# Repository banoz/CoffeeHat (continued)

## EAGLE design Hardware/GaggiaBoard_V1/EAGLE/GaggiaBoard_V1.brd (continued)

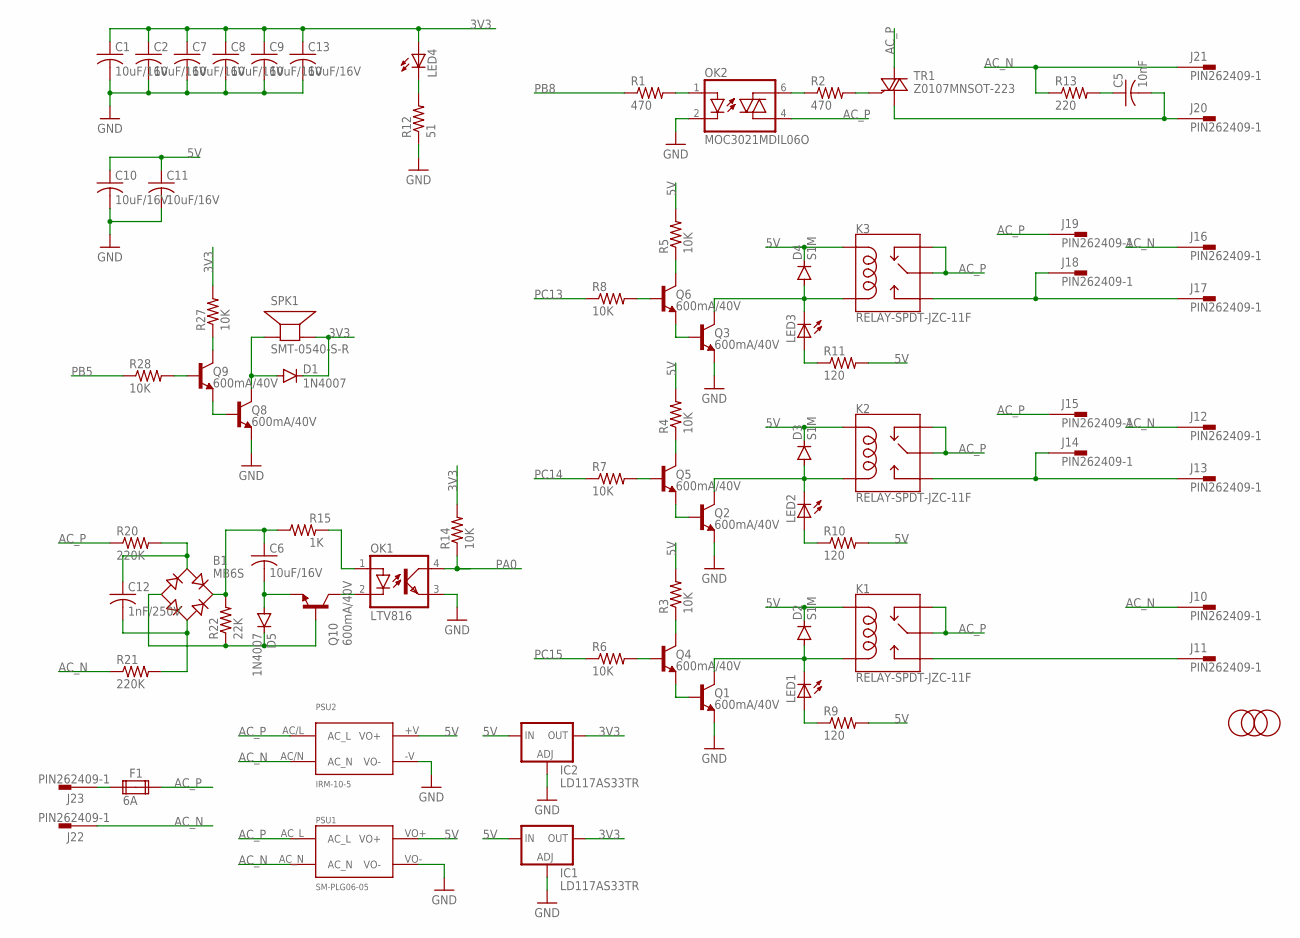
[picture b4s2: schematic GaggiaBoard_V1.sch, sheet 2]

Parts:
B1: MB6S; SOIC-4; LCSC C2487
C1, C2, C6, C7, C8, C9, C10, C11, C13: 10uF/16V; C0603; LCSC C86275
C5: 10nF; C1206; LCSC C107192
C12: 1nF/250V; C0603; LCSC C277510
D1, D5: 1N4007; DO214AC; LCSC C727081
D2, D3, D4: S1M; SMA; LCSC C155378
F1: 6A; FUSE1; LCSC C206887
IC1, IC2: LD117AS33TR; SOT223; LCSC C152529
J10, J11, J12, J13, J14, J15, J16, J17, J18, J19, J20, J21, J22, J23: PIN262409-1; 62409-1; LCSC C86495
K1, K2, K3: RELAY-SPDT-JZC-11F; RELAY-JZC; LCSC C74541
LED1, LED2, LED3, LED4: LEDCHIPLED_1206; CHIPLED_1206; LCSC C375534
MARK3, MARK4, MARK6: FIDUCIAL; FIDUCIAL_1MM
OK1: LTV816; DIL04; LCSC C2944043
OK2: MOC3021MDIL06O; DIL06O; LCSC C5242
PSU1: SM-PLG06-05; SM-PLG06
PSU2: IRM-10-5; IRM-10
Q1, Q2, Q3, Q4, Q5, Q6, Q8, Q9, Q10: 600mA/40V; SOT23-3; LCSC C82460
R1, R2: 470; R0603; LCSC C114669
R3, R4, R5, R6, R7, R8, R14, R27, R28: 10K; R0603; LCSC C98220
R9, R10, R11: 120; R0603; LCSC C114640
R12: 51; R0603; LCSC C114628
R13: 220; R2512; LCSC C877859
R15: 1K; R0603; LCSC C22548
R20, R21: 220K; R1206; LCSC C130275
R22: 22K; R0603; LCSC C114065
SPK1: SMT-0540-S-R; LCSC C391029
TR1: Z0107MNSOT-223; SOT223; LCSC C71218

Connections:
3V3: C1.1, C2.1, C7.1, C8.1, C9.1, C13.1, D1.C, IC1.4 (OUT), IC2.4 (OUT), LED4.A, R14.2, R27.2, SPK1.+ (-); also elsewhere on the board
3WAY: J11.A1, J11.A2, K1.3 (NO)
5V: C10.1, C11.1, D2.C, D3.C, D4.C, IC1.3 (IN), IC2.3 (IN), K1.5 (COIL1), K2.5 (COIL1), K3.5 (COIL1), PSU1.VO+, PSU2.+V (VO+), R3.2, R4.2, R5.2, R9.2, R10.2, R11.2; also elsewhere on the board
AC_N: J10.A1, J10.A2, J12.A1, J12.A2, J16.A1, J16.A2, J21.A1, J21.A2, J22.A1, J22.A2, PSU1.AC_N, PSU2.AC/N (AC_N), R13.1, R21.1
AC_P: F1.2A, J15.A1, J15.A2, J19.A1, J19.A2, K1.2 (NC), K1.4 (MAIN), K2.2 (NC), K2.4 (MAIN), K3.2 (NC), K3.4 (MAIN), OK2.4 (A1), PSU1.AC_L, PSU2.AC/L (AC_L), R20.1, TR1.2 (A2), TR1.4 (A2)
GND: C1.2, C2.2, C7.2, C8.2, C9.2, C10.2, C11.2, C13.2, IC1.1 (ADJ), IC2.1 (ADJ), OK1.3 (EMIT), OK2.2 (C), PSU1.VO-, PSU2.-V (VO-), Q1.2 (E), Q2.2 (E), Q3.2 (E), Q8.2 (E), R12.1; also elsewhere on the board
HEATER_1: J13.A1, J13.A2, J14.A1, J14.A2, K2.3 (NO)
HEATER_2: J17.A1, J17.A2, J18.A1, J18.A2, K3.3 (NO)
unnamed: F1.1A, J23.A1, J23.A2
unnamed: B1.-, D5.C, Q10.1 (B), R22.1
unnamed: OK1.2 (C), Q10.3 (C)
unnamed: OK2.6 (A2), R2.1
unnamed: R2.2, TR1.3 (G)
unnamed: D2.A, K1.1 (COIL2), LED1.C, Q1.3 (C)
unnamed: D3.A, K2.1 (COIL2), LED2.C, Q2.3 (C)
unnamed: D4.A, K3.1 (COIL2), LED3.C, Q3.3 (C)
unnamed: Q1.1 (B), Q4.2 (E)
unnamed: Q2.1 (B), Q5.2 (E)
unnamed: Q3.1 (B), Q6.2 (E)
unnamed: Q6.1 (B), R8.2
unnamed: Q6.3 (C), R5.1
unnamed: Q5.3 (C), R4.1
unnamed: Q5.1 (B), R7.2
unnamed: Q4.3 (C), R3.1
unnamed: Q4.1 (B), R6.2
unnamed: LED1.A, R9.1
unnamed: LED4.C, R12.2
unnamed: LED2.A, R10.1
unnamed: LED3.A, R11.1
unnamed: D1.A, Q8.3 (C), SPK1.- (+)
unnamed: C5.1, R13.2
unnamed: Q8.1 (B), Q9.2 (E)
unnamed: Q9.1 (B), R28.2
unnamed: Q9.3 (C), R27.1
unnamed: B1.~1 (AC1), C12.2, R21.2
unnamed: B1.~2 (AC2), C12.1, R20.2
unnamed: OK2.1 (A), R1.2
unnamed: C6.2, D5.A, Q10.2 (E)
unnamed: OK1.1 (A), R15.2
unnamed: B1.+, C6.1, R15.1, R22.2
PA0: OK1.4 (COL), R14.1; also elsewhere on the board
PB5: R28.1; also elsewhere on the board
PB8: R1.1; also elsewhere on the board
PC13: R8.1; also elsewhere on the board
PC14: R7.1; also elsewhere on the board
PC15: R6.1; also elsewhere on the board
PUMP_P: C5.2, J20.A1, J20.A2, TR1.1 (A1)

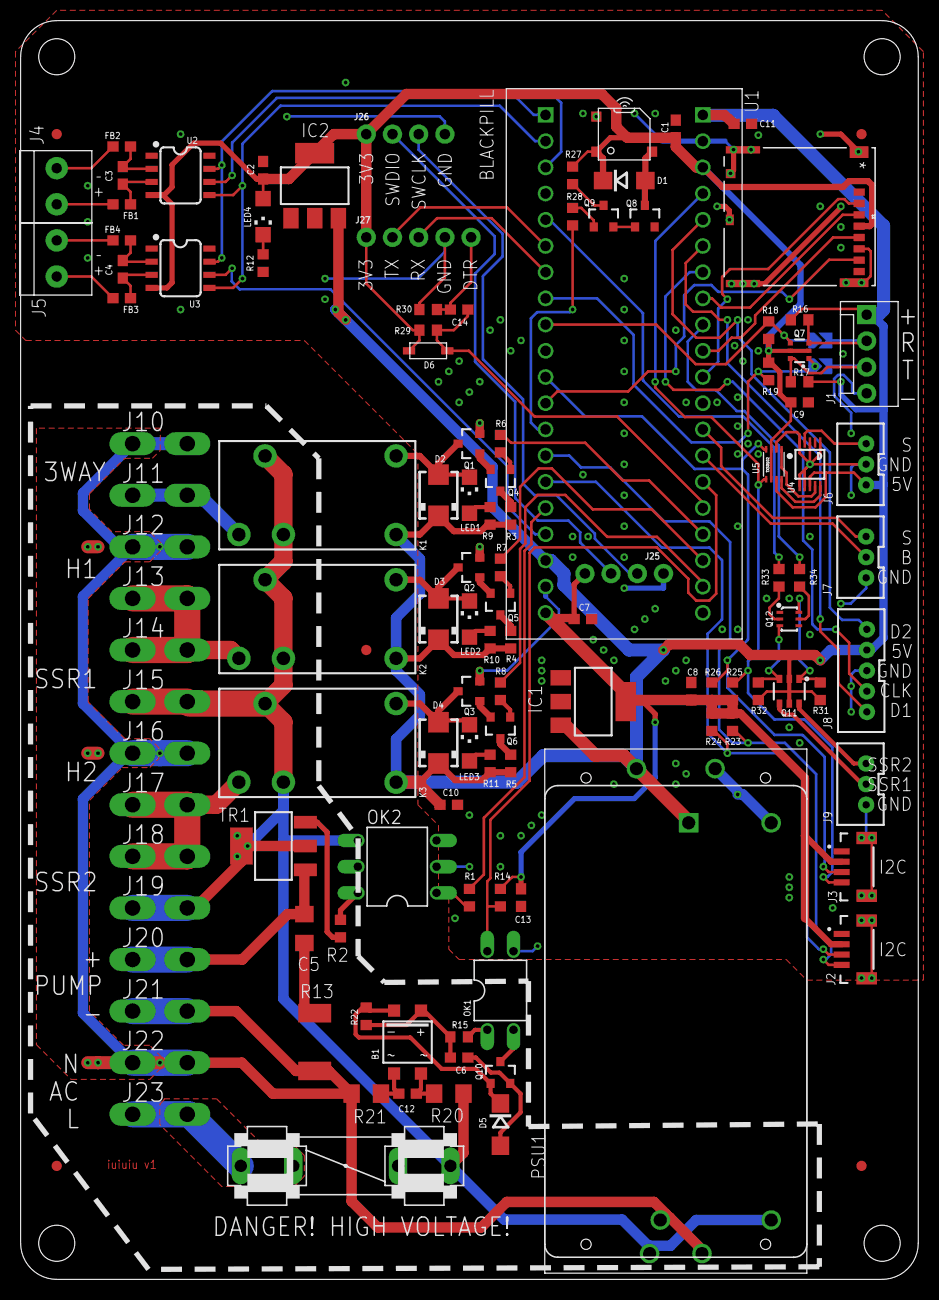
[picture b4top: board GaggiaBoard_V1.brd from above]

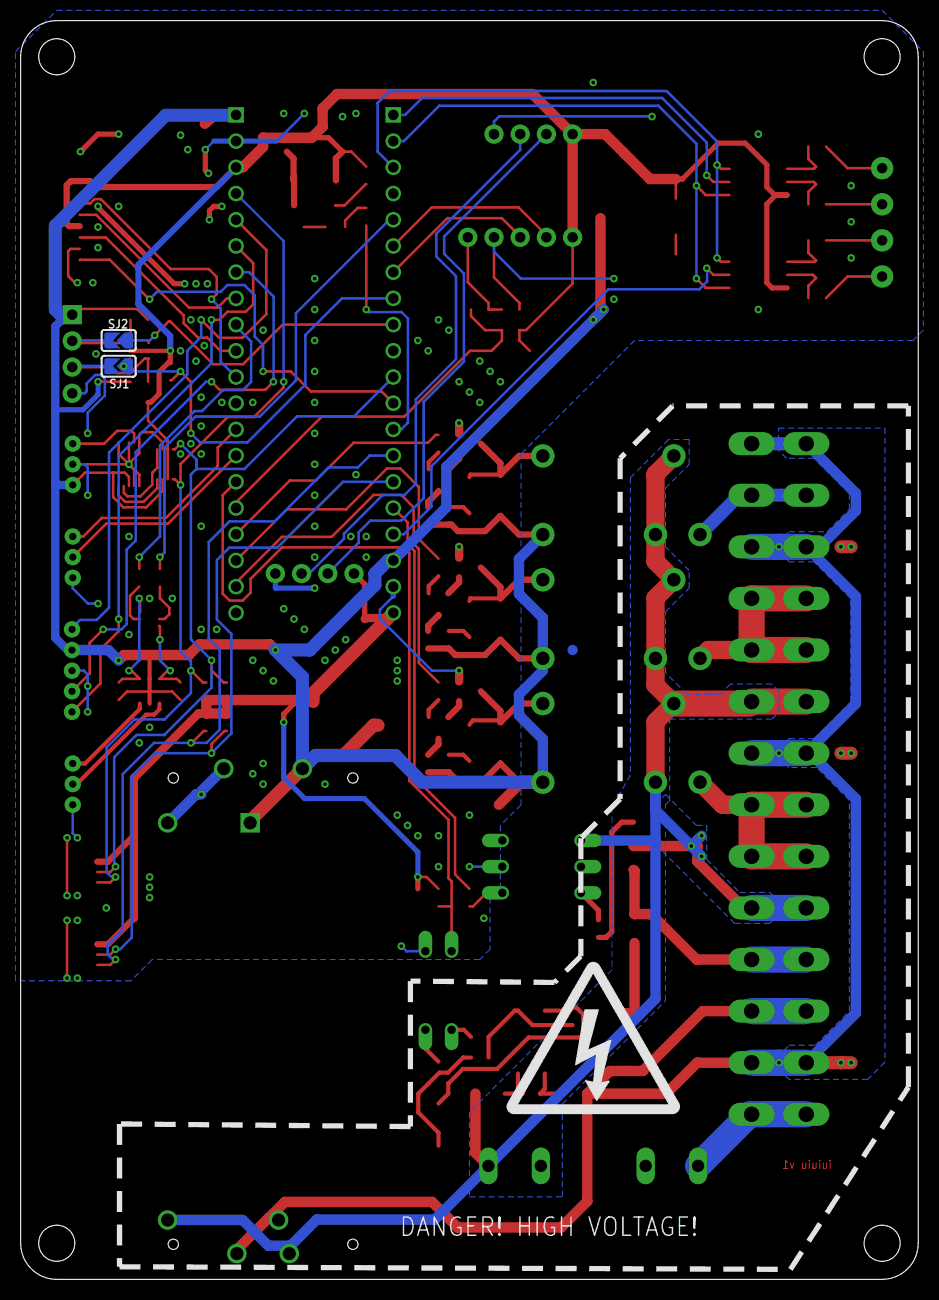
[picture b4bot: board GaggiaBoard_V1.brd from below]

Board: 2 copper layers, 87.0 x 122.0 mm, 128 parts (4 on the bottom side), 93 nets.

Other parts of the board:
U$1: HV_LOGO_3

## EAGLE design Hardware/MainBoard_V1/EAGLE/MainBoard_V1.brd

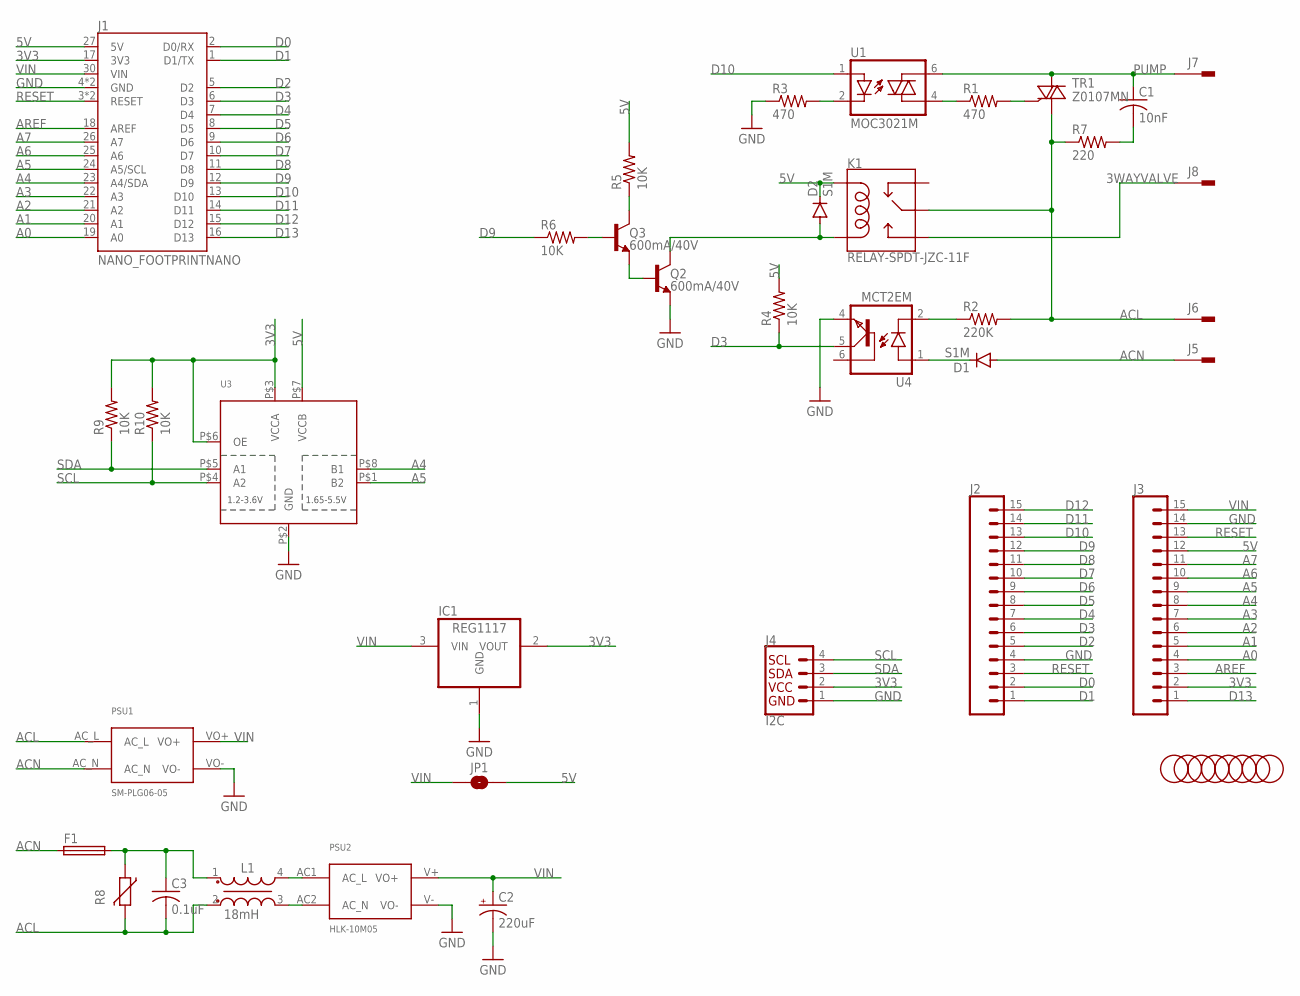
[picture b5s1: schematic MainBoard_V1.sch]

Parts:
C1: 10nF; C075-032X103; LCSC C2893639
C2: 220uF; E2,5-6
C3: 0.1uF; C150-054X183
D1, D2: S1M; SMA; LCSC C155378
F1: FUSETE5; TE5
IC1: REG1117; SOT223; LCSC C26537
J1: NANO_FOOTPRINTNANO; NANO
J2, J3: CONN_15; 1X15; LCSC C2894938
J4: I2C; JST04_1MM_VERT; LCSC C160390
J5, J6, J7, J8: PIN262409-1; 62409-1; LCSC C305817
JP1: JUMPER-SMT_2_NO_SILK; SMT-JUMPER_2_NO_SILK
K1: RELAY-SPDT-JZC-11F; RELAY-JZC; LCSC C74541
L1: 18mH; WE-TFC_UU9.8V
PSU1: SM-PLG06-05; SM-PLG06
PSU2: HLK-10M05; HLK-10MXX
Q2, Q3: 600mA/40V; SOT23-3; LCSC C82460
R1, R3: 470; R0603; LCSC C23179
R2: 220K; R0603; LCSC C22961
R4, R5, R6, R9, R10: 10K; R0603; LCSC C98220
R7: 220; R2512; LCSC C38808
R8: VARISTOR-7,5; R-7,5
TR1: Z0107MN; SOT223; LCSC C145130
U1: MOC3021M; DIL06; LCSC C123202
U3: TXS0102; VFSOP-8; LCSC C2677417
U4: MCT2EM; PDIP6_8P89X6P60_ONS; LCSC C258259
U$1, U$2, U$3, U$4, U$5, U$6, U$7, U$8: FIDUCIAL; FIDUCIAL_1MM

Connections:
3V3: IC1.2 (VOUT), J1.17 (3V3), J3.2, J4.2, R9.2, R10.2, U3.P$3 (VCCA), U3.P$6 (OE)
3WAYVALVE: J8.A1, J8.A2, K1.3 (NO)
5V: D2.C, J1.27 (5V), J3.12, JP1.2, K1.5 (COIL1), R4.2, R5.2, U3.P$7 (VCCB)
A0: J1.19 (A0), J3.4
A1: J1.20 (A1), J3.5
A2: J1.21 (A2), J3.6
A3: J1.22 (A3), J3.7
A4: J1.23 (A4/SDA), J3.8, U3.P$8 (B1)
A5: J1.24 (A5/SCL), J3.9, U3.P$1 (B2)
A6: J1.25 (A6), J3.10
A7: J1.26 (A7), J3.11
ACL: C3.2, J6.A1, J6.A2, K1.4 (MAIN), L1.2, PSU1.AC_L, R2.2, R7.1, R8.2, TR1.1 (A1)
ACN: D1.A, F1.1, J5.A1, J5.A2, PSU1.AC_N
ACN1: C3.1, F1.2, L1.1, R8.1
AREF: J1.18 (AREF), J3.3
D0: J1.2 (D0/RX), J2.2
D1: J1.1 (D1/TX), J2.1
D2: J1.5 (D2), J2.5
D3: J1.6 (D3), J2.6, R4.1, U4.5 (COL)
D4: J1.7 (D4), J2.7
D5: J1.8 (D5), J2.8
D6: J1.9 (D6), J2.9
D7: J1.10 (D7), J2.10
D8: J1.11 (D8), J2.11
D9: J1.12 (D9), J2.12, R6.1
D10: J1.13 (D10), J2.13, U1.1 (A)
D11: J1.14 (D11), J2.14
D12: J1.15 (D12), J2.15
D13: J1.16 (D13), J3.1
GND: C2.-, IC1.1 (GND), J1.4 (GND), J1.29 (GND), J2.4, J3.14, J4.1, PSU1.VO-, PSU2.V- (VO-), Q2.2 (E), R3.1, U3.P$2 (GND), U4.4 (EMI)
unnamed: R1.1, U1.4 (A1)
unnamed: R1.2, TR1.3 (G)
unnamed: R3.2, U1.2 (C)
unnamed: C1.2, R7.2
unnamed: R2.1, U4.2 (C)
unnamed: D1.C, U4.1 (A)
unnamed: L1.4, PSU2.AC1 (AC_L)
unnamed: Q2.1 (B), Q3.2 (E)
unnamed: D2.A, K1.1 (COIL2), Q2.3 (C)
unnamed: Q3.3 (C), R5.1
unnamed: Q3.1 (B), R6.2
unnamed: L1.3, PSU2.AC2 (AC_N)
PUMP: C1.1, J7.A1, J7.A2, TR1.2 (A2), TR1.4 (A2), U1.6 (A2)
RESET: J1.3 (RESET), J1.28 (RESET), J2.3, J3.13
SCL: J4.4, R10.1, U3.P$4 (A2)
SDA: J4.3, R9.1, U3.P$5 (A1)
VIN: C2.+, IC1.3 (VIN), J1.30 (VIN), J3.15, JP1.1, PSU1.VO+, PSU2.V+ (VO+)

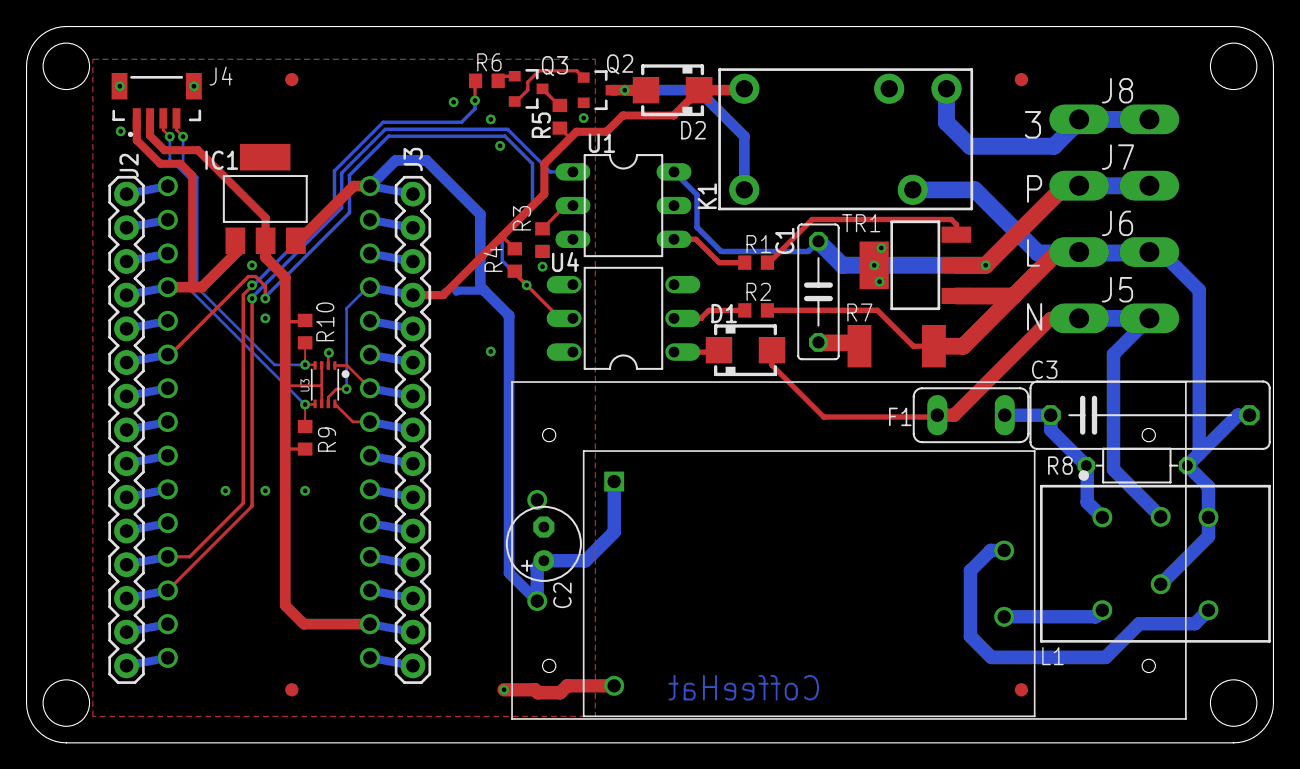
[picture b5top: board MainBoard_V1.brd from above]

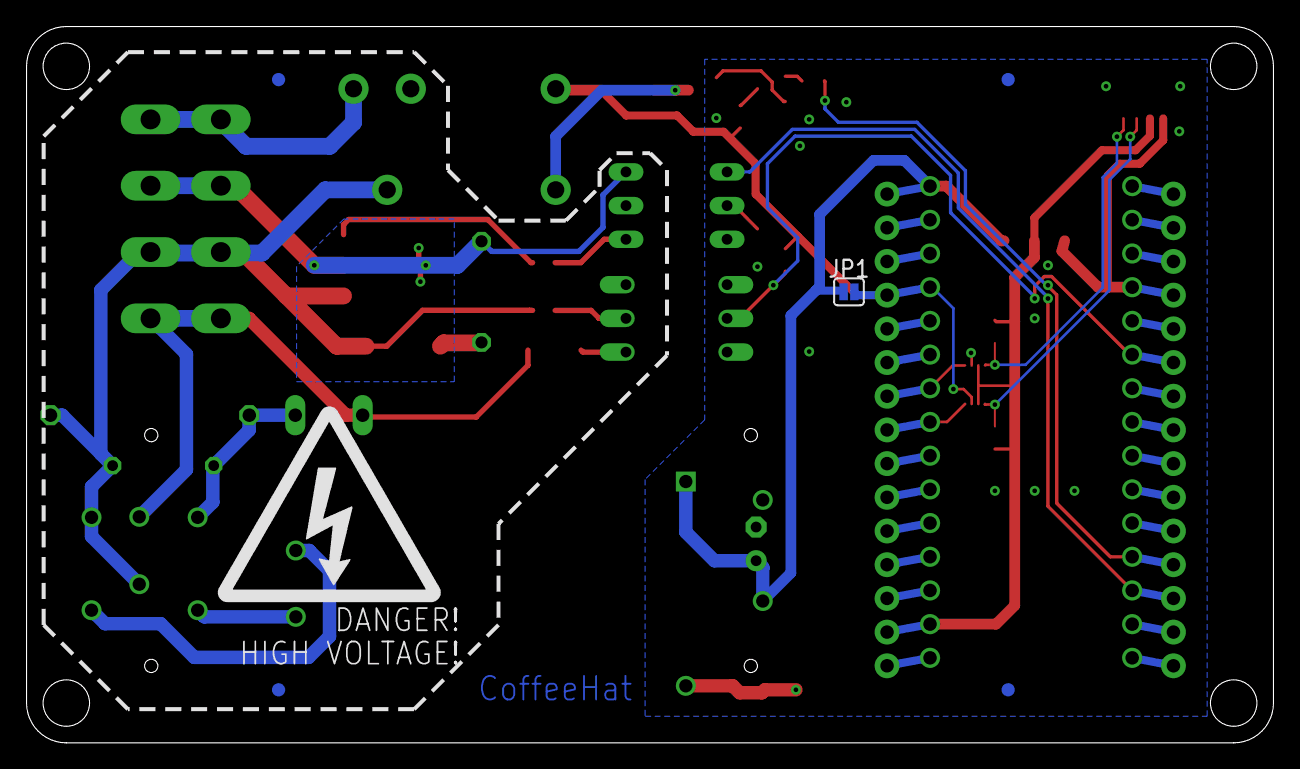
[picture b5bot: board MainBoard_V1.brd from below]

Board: 2 copper layers, 94.0 x 54.0 mm, 45 parts (6 on the bottom side), 47 nets.

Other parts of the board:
U$9: HV_LOGO_3

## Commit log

2021-12-03 Create LICENSE
2021-12-03 Initial state
2021-12-03 Gerber files (alpha version)
2021-12-19 Bug fix
2021-12-22 New folder structure
2021-12-23 Fiducials added
2021-12-23 Exports added
2021-12-23 README changed
2021-12-23 UART level shifter
2022-02-04 SubBoard_V1 initial state
2022-02-07 Mounting holes
2022-02-08 Layout optimization
2022-02-09 All SMD to the top layer
2022-02-10 SubBoard exports
2022-02-10 MainBoard BOM update
2022-02-10 GaggiaBoard BOM update
2022-02-16 Warning symbols added
2022-03-04 Switch pullups added
2022-03-13 I2C pullups
2022-04-22 Layout change
2022-04-22 Boiler SSR pin relocation
2022-04-22 Spade connectors BOM fix
2022-05-02 Nextion full buffer IO
2022-05-09 PSU replaced
2022-05-09 Pin assignment updated
2022-05-10 MEAN WELL PSU option, discrete level shifters
2022-05-10 TXU0102 level shifter for SSRs
2022-05-14 UARTs reassigned, LEDs fixed
2022-05-21 Connectors spacing fixed
2022-06-03 Layout update
2022-06-05 Scales port change to PB
2022-06-10 Connector spacing fixed
2022-06-10 Pump bridge rectifier removed, SSR control changed
2022-06-18 Switch reassignment
2022-07-08 V2 initial state
2022-08-14 part list fix
2022-09-16 V2.1 update
2022-09-16 Update README.md
    Removed SD card related info.
2022-09-18 V3 added
2022-09-18 UART added
2022-09-23 README + PC13 load fix
2022-09-25 Centroid added to Gerber
2022-09-28 J1 fix
2022-11-03 5V supply fix
2022-11-05 stl links
2022-11-17 3-Way valve SSR
2022-11-29 snubbers
2023-02-25 J4 p/n fix
2023-03-05 Faston drill fix
2023-03-16 Steam boiler relays repurpose
2023-03-29 OK1 part change
2023-08-29 pull downs on GPIO outputs
2023-10-17 Copper pour cutouts for TC
2024-01-21 Snubber change
2025-03-26 v4 schematics
2025-10-02 CleverBoard_V1
